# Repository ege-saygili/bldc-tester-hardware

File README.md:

# BLDC Tester Hardware

This repository contains the hardware design files for the BLDC Tester project. It works in conjunction with the [BLDC_Tester](https://github.com/ege-saygili/bldc-tester) software repository.

## Repository Structure
This repository includes:
- PCB design files
- Schematics
- Component libraries
- Documentation

## Related Repositories
- [BLDC_Tester](https://github.com/ege-saygili/bldc-tester) - Software repository containing the firmware and control software for this hardware

## Project Overview
The BLDC Tester is a comprehensive testing platform for Brushless DC motors, combining this hardware with dedicated control software to perform various motor tests and measurements.

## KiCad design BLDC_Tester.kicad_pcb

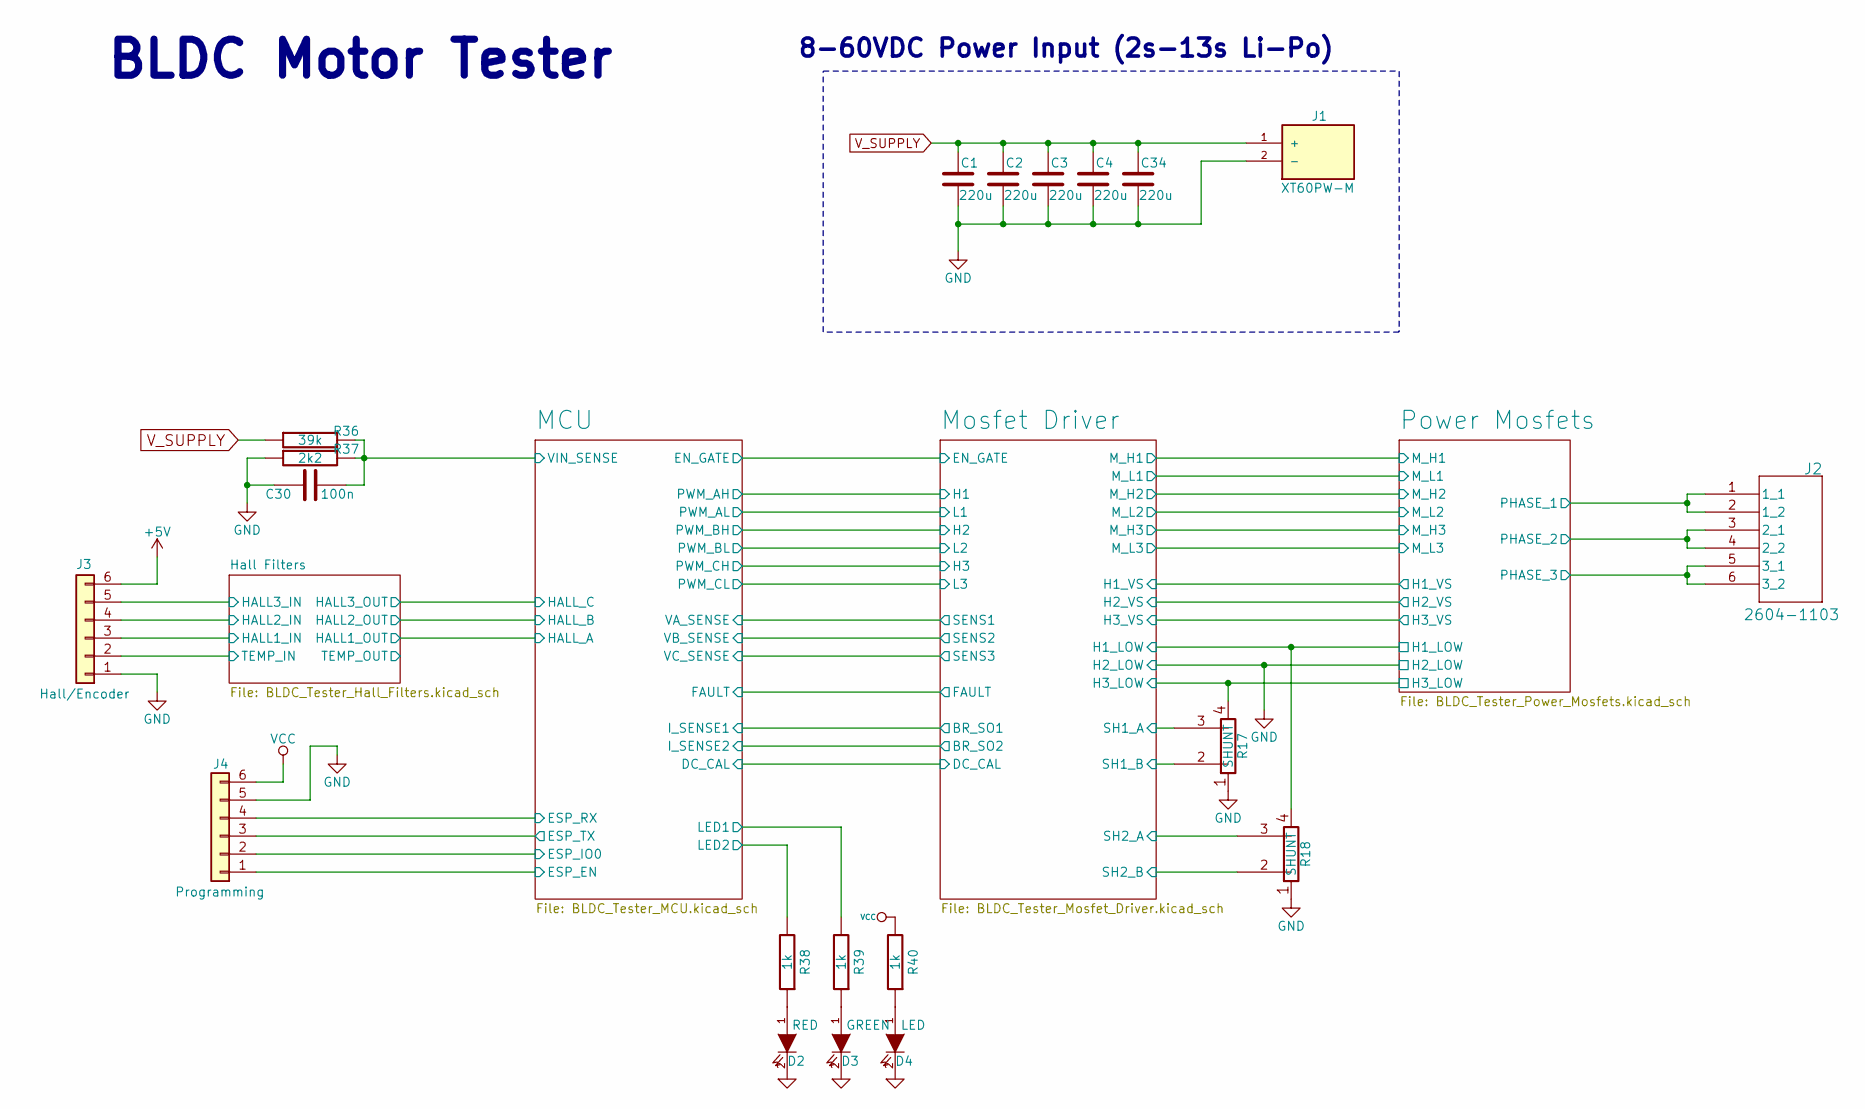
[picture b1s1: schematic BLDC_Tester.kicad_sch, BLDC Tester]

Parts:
C1, C2, C3, C4, C34: 220u; CP_Radial_D10.0mm_P5.00mm
C30: 100n; C_0603_1608Metric
D2: RED; LED_0603_1608Metric
D3: GREEN; LED_0603_1608Metric
D4: LED; LED_0603_1608Metric
J1: XT60PW-M; AMASS_XT60PW-M; PARTREV V1.2
J2: 2604-1103; CONN3_2604-1103_WAG
J3: Hall/Encoder; JST_PH_S6B-PH-SM4-TB_1x06-1MP_P2.00mm_Horizontal
J4: Programming; PinHeader_1x06_P2.54mm_Vertical
R17, R18: SHUNT; RES_BVS-3920_ISA
R36: 39k; R_0603_1608Metric
R37: 2k2; R_0603_1608Metric
R38, R39, R40: 1k; R_0603_1608Metric

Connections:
+5V: J3.6; also elsewhere on the board
/Hall Filters/HALL1_IN: J3.3; also elsewhere on the board
/Hall Filters/HALL2_IN: J3.4; also elsewhere on the board
/Hall Filters/HALL3_IN: J3.5; also elsewhere on the board
/Hall Filters/TEMP_MOTOR: J3.2; also elsewhere on the board
/MCU/ESP_EN: J4.1; also elsewhere on the board
/MCU/ESP_IO0: J4.2; also elsewhere on the board
/MCU/ESP_RX: J4.4; also elsewhere on the board
/MCU/ESP_TX: J4.3; also elsewhere on the board
/MCU/LED1: R39.2; also elsewhere on the board
/MCU/LED2: R38.2; also elsewhere on the board
/MCU/VIN_SENSE: C30.2, R36.2, R37.2; also elsewhere on the board
/Mosfet Driver/H1_LOW: R18.4; also elsewhere on the board
/Mosfet Driver/H1_VS: J2.1 (1_1), J2.2 (1_2); also elsewhere on the board
/Mosfet Driver/H2_VS: J2.3 (2_1), J2.4 (2_2); also elsewhere on the board
/Mosfet Driver/H3_LOW: R17.4; also elsewhere on the board
/Mosfet Driver/H3_VS: J2.5 (3_1), J2.6 (3_2); also elsewhere on the board
/Mosfet Driver/SH1_A: R17.3; also elsewhere on the board
/Mosfet Driver/SH1_B: R17.2; also elsewhere on the board
/Mosfet Driver/SH2_A: R18.3; also elsewhere on the board
/Mosfet Driver/SH2_B: R18.2; also elsewhere on the board
GND: C1.2, C2.2, C3.2, C4.2, C30.1, C34.2, D2.2 (K), D3.2 (K), D4.2 (K), J1.2 (-), J3.1, J4.5, R17.1, R18.1, R37.1; also elsewhere on the board
unnamed: D2.1 (A), R38.1
unnamed: D3.1 (A), R39.1
unnamed: D4.1 (A), R40.1
VCC: J4.6, R40.2; also elsewhere on the board
V_SUPPLY: C1.1, C2.1, C3.1, C4.1, C34.1, J1.1 (+), R36.1; also elsewhere on the board

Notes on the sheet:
BLDC Motor Tester
8-60VDC Power Input (2s-13s Li-Po)

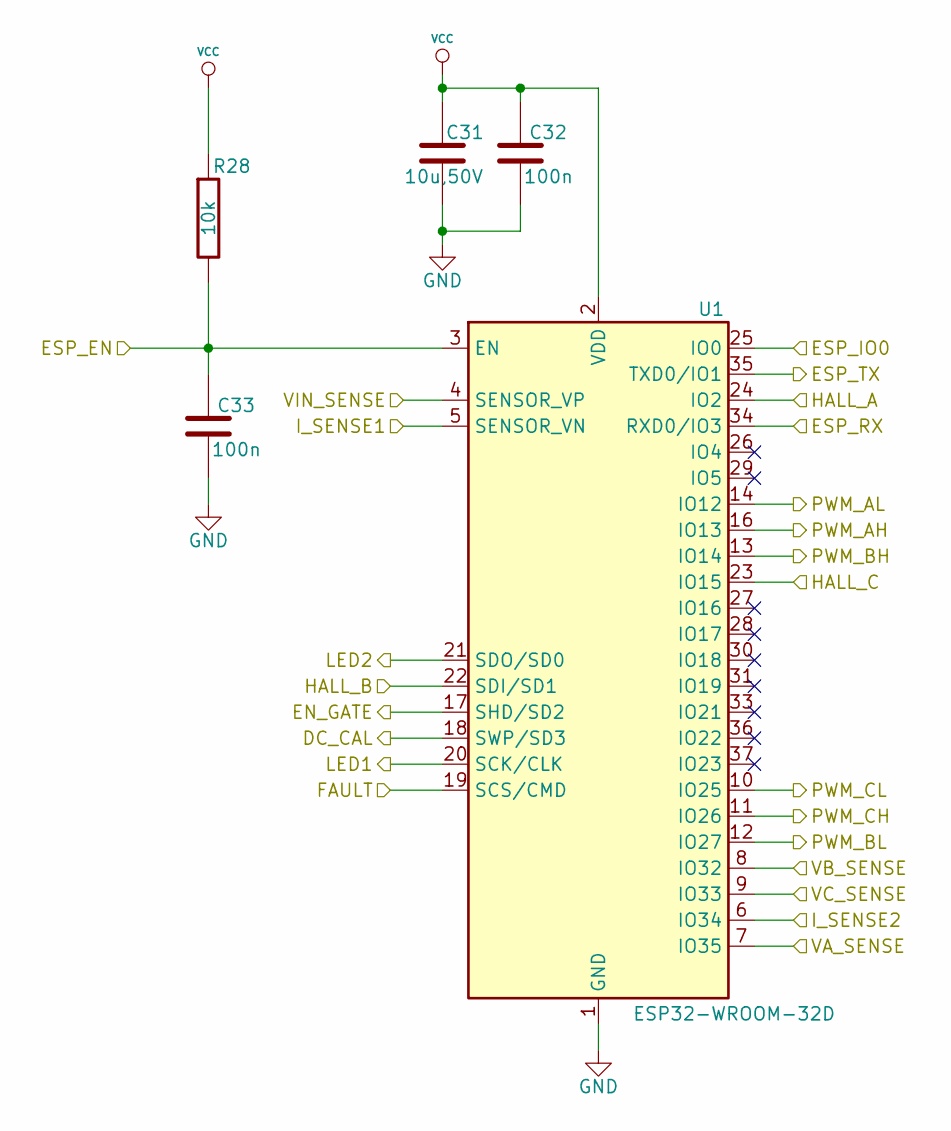
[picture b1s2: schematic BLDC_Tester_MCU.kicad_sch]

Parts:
C31: 10u,50V; C_1206_3216Metric
C32, C33: 100n; C_0603_1608Metric
R28: 10k; R_0603_1608Metric
U1: ESP32-WROOM-32D

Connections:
/Hall Filters/HALL1_OUT: U1.24 (IO2); also elsewhere on the board
/Hall Filters/HALL2_OUT: U1.22 (SDI/SD1); also elsewhere on the board
/Hall Filters/HALL3_OUT: U1.23 (IO15); also elsewhere on the board
/MCU/DC_CAL: U1.18 (SWP/SD3); also elsewhere on the board
/MCU/EN_GATE: U1.17 (SHD/SD2); also elsewhere on the board
/MCU/ESP_EN: C33.1, R28.2, U1.3 (EN); also elsewhere on the board
/MCU/ESP_IO0: U1.25 (IO0); also elsewhere on the board
/MCU/ESP_RX: U1.34 (RXD0/IO3); also elsewhere on the board
/MCU/ESP_TX: U1.35 (TXD0/IO1); also elsewhere on the board
/MCU/FAULT: U1.19 (SCS/CMD); also elsewhere on the board
/MCU/I_SENSE1: U1.5 (SENSOR_VN); also elsewhere on the board
/MCU/I_SENSE2: U1.6 (IO34); also elsewhere on the board
/MCU/LED1: U1.20 (SCK/CLK); also elsewhere on the board
/MCU/LED2: U1.21 (SDO/SD0); also elsewhere on the board
/MCU/PWM_AH: U1.16 (IO13); also elsewhere on the board
/MCU/PWM_AL: U1.14 (IO12); also elsewhere on the board
/MCU/PWM_BH: U1.13 (IO14); also elsewhere on the board
/MCU/PWM_BL: U1.12 (IO27); also elsewhere on the board
/MCU/PWM_CH: U1.11 (IO26); also elsewhere on the board
/MCU/PWM_CL: U1.10 (IO25); also elsewhere on the board
/MCU/VA_SENSE: U1.7 (IO35); also elsewhere on the board
/MCU/VB_SENSE: U1.8 (IO32); also elsewhere on the board
/MCU/VC_SENSE: U1.9 (IO33); also elsewhere on the board
/MCU/VIN_SENSE: U1.4 (SENSOR_VP); also elsewhere on the board
GND: C31.2, C32.2, C33.2, U1.1 (GND), U1.15 (GND), U1.38 (GND), U1.39 (GND); also elsewhere on the board
VCC: C31.1, C32.1, R28.1, U1.2 (VDD); also elsewhere on the board

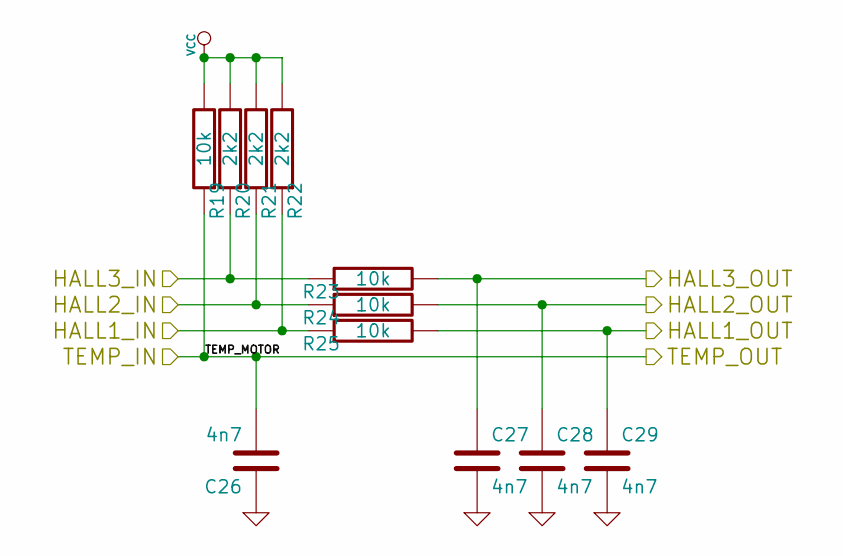
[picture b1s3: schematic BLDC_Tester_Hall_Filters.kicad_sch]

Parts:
C26, C27, C28, C29: 4n7; C_0603_1608Metric
R19, R23, R24, R25: 10k; R_0603_1608Metric
R20, R21, R22: 2k2; R_0603_1608Metric

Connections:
/Hall Filters/HALL1_IN: R22.1, R25.1; also elsewhere on the board
/Hall Filters/HALL1_OUT: C29.1, R25.2; also elsewhere on the board
/Hall Filters/HALL2_IN: R21.1, R24.1; also elsewhere on the board
/Hall Filters/HALL2_OUT: C28.1, R24.2; also elsewhere on the board
/Hall Filters/HALL3_IN: R20.1, R23.1; also elsewhere on the board
/Hall Filters/HALL3_OUT: C27.1, R23.2; also elsewhere on the board
/Hall Filters/TEMP_MOTOR: C26.2, R19.1; also elsewhere on the board
GND: C26.1, C27.2, C28.2, C29.2; also elsewhere on the board
VCC: R19.2, R20.2, R21.2, R22.2; also elsewhere on the board

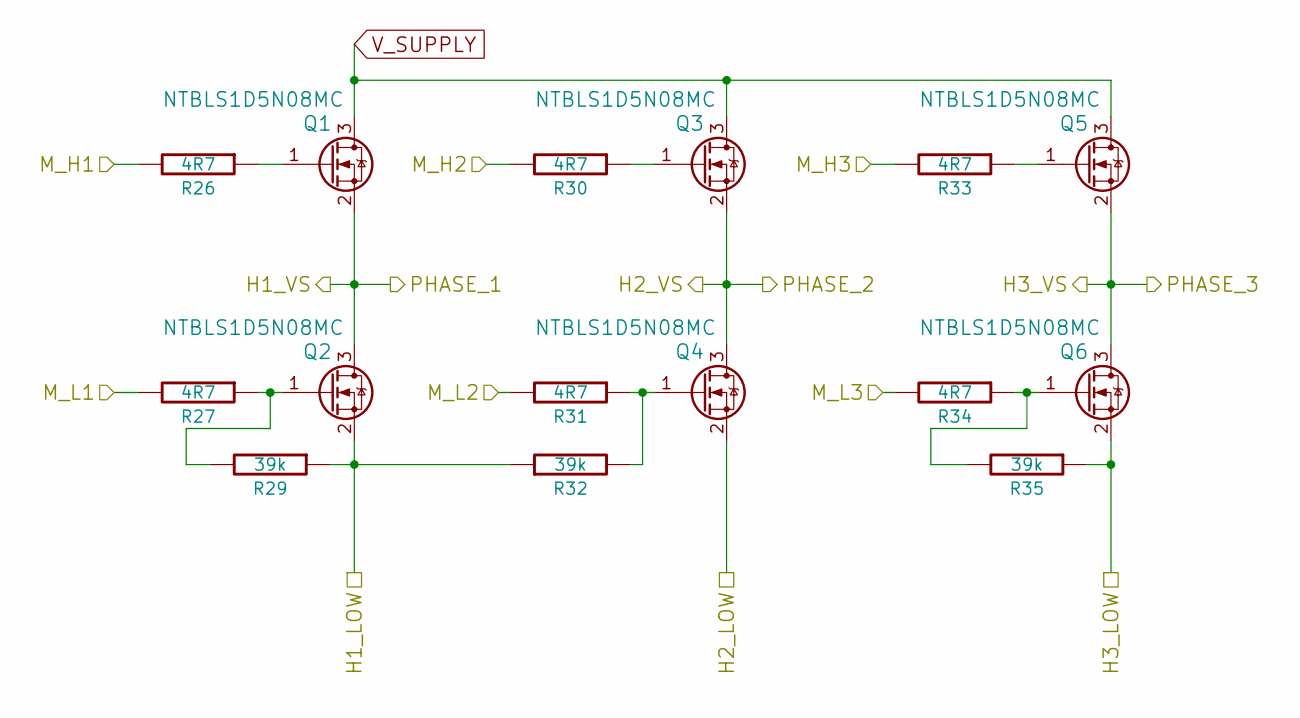
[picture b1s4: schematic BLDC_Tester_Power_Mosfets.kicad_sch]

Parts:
Q1, Q2, Q3, Q4, Q5, Q6: NTBLS1D5N08MC; Infineon_PG-HSOF-8-1
R26, R27, R30, R31, R33, R34: 4R7; R_0603_1608Metric
R29, R32, R35: 39k; R_0603_1608Metric

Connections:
/Mosfet Driver/H1_LOW: Q2.2 (S), R29.1, R32.1; also elsewhere on the board
/Mosfet Driver/H1_VS: Q1.2 (S), Q2.3 (D); also elsewhere on the board
/Mosfet Driver/H2_VS: Q3.2 (S), Q4.3 (D); also elsewhere on the board
/Mosfet Driver/H3_LOW: Q6.2 (S), R35.1; also elsewhere on the board
/Mosfet Driver/H3_VS: Q5.2 (S), Q6.3 (D); also elsewhere on the board
/Mosfet Driver/M_H1: R26.2; also elsewhere on the board
/Mosfet Driver/M_H2: R30.2; also elsewhere on the board
/Mosfet Driver/M_H3: R33.2; also elsewhere on the board
/Mosfet Driver/M_L1: R27.2; also elsewhere on the board
/Mosfet Driver/M_L2: R31.2; also elsewhere on the board
/Mosfet Driver/M_L3: R34.2; also elsewhere on the board
GND: Q4.2 (S); also elsewhere on the board
unnamed: Q1.1 (G), R26.1
unnamed: Q2.1 (G), R27.1, R29.2
unnamed: Q3.1 (G), R30.1
unnamed: Q4.1 (G), R31.1, R32.2
unnamed: Q5.1 (G), R33.1
unnamed: Q6.1 (G), R34.1, R35.2
V_SUPPLY: Q1.3 (D), Q3.3 (D), Q5.3 (D); also elsewhere on the board

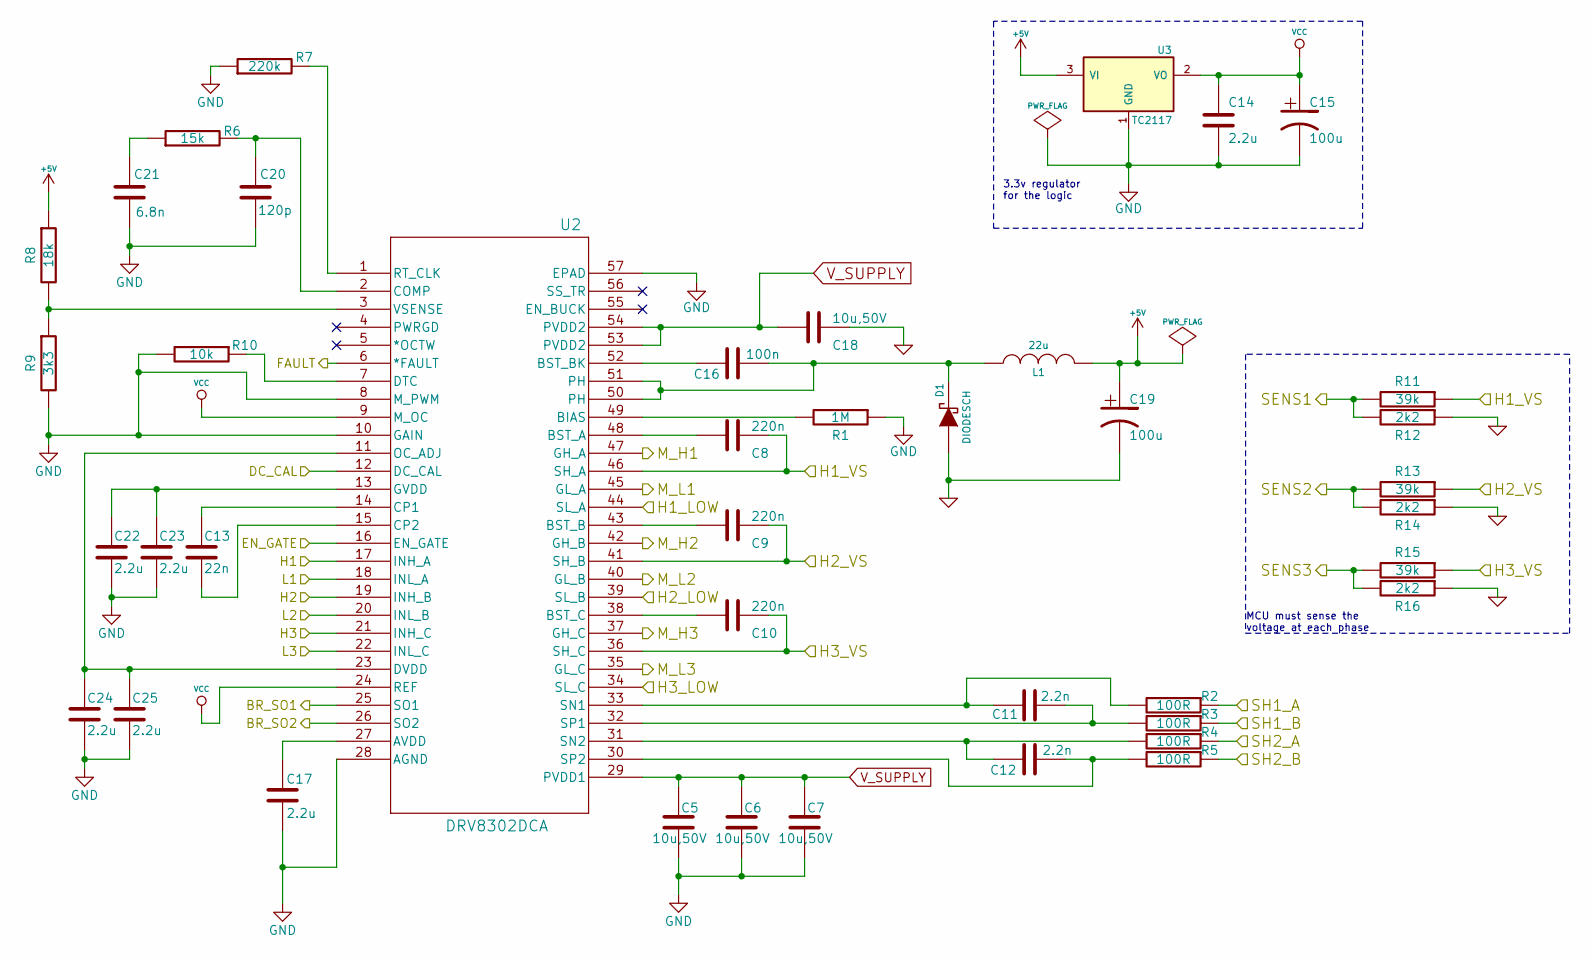
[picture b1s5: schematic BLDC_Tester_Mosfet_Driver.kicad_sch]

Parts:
C5, C6, C7, C18: 10u,50V; C_1206_3216Metric
C8, C9, C10: 220n; C_0603_1608Metric
C11, C12: 2.2n; C_0603_1608Metric
C13: 22n; C_0603_1608Metric
C14, C17, C22, C23, C24, C25: 2.2u; C_0603_1608Metric
C15, C19: 100u; CP_EIA-3528-21_Kemet-B
C16: 100n; C_0603_1608Metric
C20: 120p; C_0603_1608Metric
C21: 6.8n; C_0603_1608Metric
D1: DIODESCH; D_SMA
L1: 22u; L_12x12mm_H4.5mm
R1: 1M; R_0603_1608Metric
R2, R3, R4, R5: 100R; R_0603_1608Metric
R6: 15k; R_0603_1608Metric
R7: 220k; R_0603_1608Metric
R8: 18k; R_0603_1608Metric
R9: 3k3; R_0603_1608Metric
R10: 10k; R_0603_1608Metric
R11, R13, R15: 39k; R_0603_1608Metric
R12, R14, R16: 2k2; R_0603_1608Metric
U2: DRV8302DCA; DCA56_6P35X3P61
U3: TC2117; SOT-223-3_TabPin2

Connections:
+5V: C19.1, L1.2, R8.1, U3.3 (VI); also elsewhere on the board
/MCU/DC_CAL: U2.12 (DC_CAL); also elsewhere on the board
/MCU/EN_GATE: U2.16 (EN_GATE); also elsewhere on the board
/MCU/FAULT: U2.6 (*FAULT); also elsewhere on the board
/MCU/I_SENSE1: U2.25 (SO1); also elsewhere on the board
/MCU/I_SENSE2: U2.26 (SO2); also elsewhere on the board
/MCU/PWM_AH: U2.17 (INH_A); also elsewhere on the board
/MCU/PWM_AL: U2.18 (INL_A); also elsewhere on the board
/MCU/PWM_BH: U2.19 (INH_B); also elsewhere on the board
/MCU/PWM_BL: U2.20 (INL_B); also elsewhere on the board
/MCU/PWM_CH: U2.21 (INH_C); also elsewhere on the board
/MCU/PWM_CL: U2.22 (INL_C); also elsewhere on the board
/MCU/VA_SENSE: R11.2, R12.2; also elsewhere on the board
/MCU/VB_SENSE: R13.2, R14.2; also elsewhere on the board
/MCU/VC_SENSE: R15.2, R16.2; also elsewhere on the board
/Mosfet Driver/H1_LOW: U2.44 (SL_A); also elsewhere on the board
/Mosfet Driver/H1_VS: C8.1, R11.1, U2.46 (SH_A); also elsewhere on the board
/Mosfet Driver/H2_VS: C9.1, R13.1, U2.41 (SH_B); also elsewhere on the board
/Mosfet Driver/H3_LOW: U2.34 (SL_C); also elsewhere on the board
/Mosfet Driver/H3_VS: C10.1, R15.1, U2.36 (SH_C); also elsewhere on the board
/Mosfet Driver/M_H1: U2.47 (GH_A); also elsewhere on the board
/Mosfet Driver/M_H2: U2.42 (GH_B); also elsewhere on the board
/Mosfet Driver/M_H3: U2.37 (GH_C); also elsewhere on the board
/Mosfet Driver/M_L1: U2.45 (GL_A); also elsewhere on the board
/Mosfet Driver/M_L2: U2.40 (GL_B); also elsewhere on the board
/Mosfet Driver/M_L3: U2.35 (GL_C); also elsewhere on the board
/Mosfet Driver/SH1_A: R2.1; also elsewhere on the board
/Mosfet Driver/SH1_B: R3.1; also elsewhere on the board
/Mosfet Driver/SH2_A: R4.1; also elsewhere on the board
/Mosfet Driver/SH2_B: R5.1; also elsewhere on the board
GND: C5.2, C6.2, C7.2, C14.2, C15.2, C17.1, C18.1, C19.2, C20.2, C21.2, C22.2, C23.2, C24.2, C25.2, D1.1 (A), R1.1, R7.1, R9.2, R10.2, R12.1, R14.1, R16.1, U2.8 (M_PWM), U2.10 (GAIN), U2.28 (AGND), U2.39 (SL_B), U2.57 (EPAD), U3.1 (GND); also elsewhere on the board
unnamed: C21.1, R6.1
unnamed: C16.1, D1.2 (K), L1.1, U2.50 (PH), U2.51 (PH)
unnamed: C17.2, U2.27 (AVDD)
unnamed: R1.2, U2.49 (BIAS)
unnamed: C8.2, U2.48 (BST_A)
unnamed: C9.2, U2.43 (BST_B)
unnamed: C16.2, U2.52 (BST_BK)
unnamed: C10.2, U2.38 (BST_C)
unnamed: C20.1, R6.2, U2.2 (COMP)
unnamed: C13.1, U2.14 (CP1)
unnamed: C13.2, U2.15 (CP2)
unnamed: R10.1, U2.7 (DTC)
unnamed: C24.1, C25.1, U2.11 (OC_ADJ), U2.23 (DVDD)
unnamed: C22.1, C23.1, U2.13 (GVDD)
unnamed: R7.2, U2.1 (RT_CLK)
unnamed: C11.1, R2.2, U2.33 (SN1)
unnamed: C12.1, R4.2, U2.31 (SN2)
unnamed: C11.2, R3.2, U2.32 (SP1)
unnamed: C12.2, R5.2, U2.30 (SP2)
unnamed: R8.2, R9.1, U2.3 (VSENSE)
VCC: C14.1, C15.1, U2.9 (M_OC), U2.24 (REF), U3.2 (VO); also elsewhere on the board
V_SUPPLY: C5.1, C6.1, C7.1, C18.2, U2.29 (PVDD1), U2.53 (PVDD2), U2.54 (PVDD2); also elsewhere on the board

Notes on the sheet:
MCU must sense the voltage at each phase
3.3v regulator for the logic

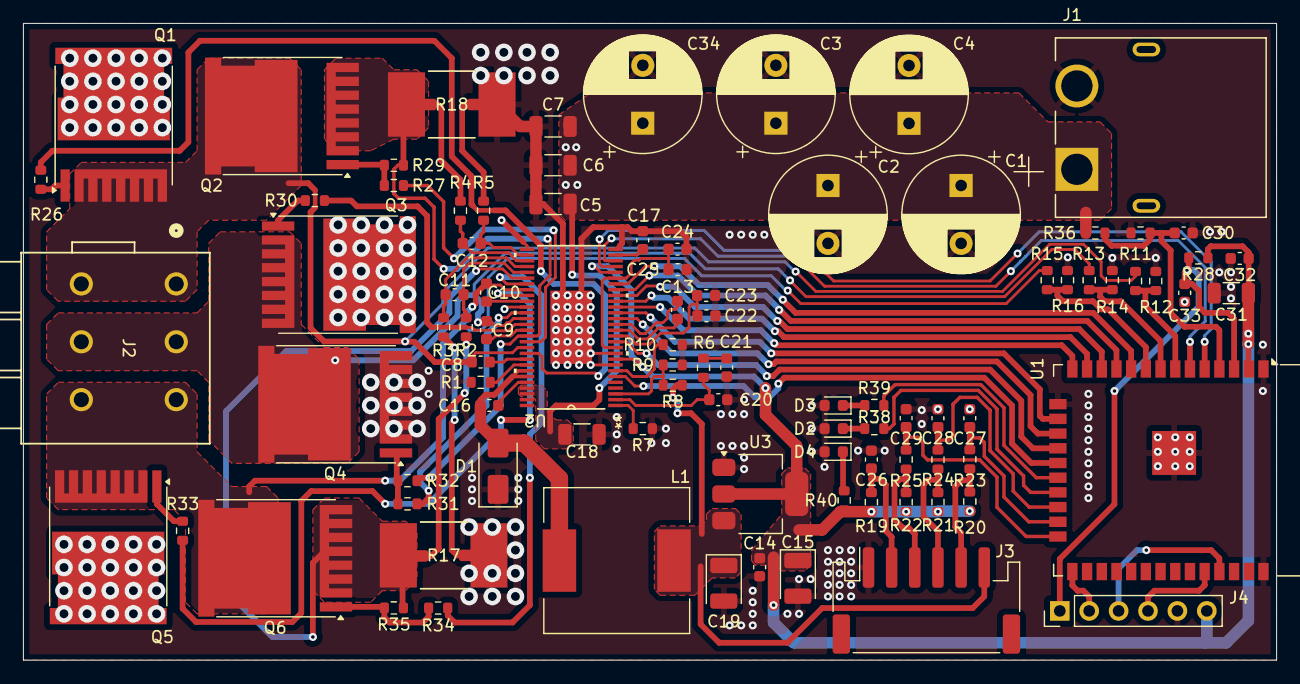
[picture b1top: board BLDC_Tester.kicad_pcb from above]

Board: 2 copper layers, 108.2 x 55.0 mm, 92 parts (0 on the bottom side), 76 nets.

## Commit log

2024-11-26 Initial hardware files commit
2024-11-26 README added
